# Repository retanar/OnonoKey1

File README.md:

# OnonoKey1 split keyboard

### Sources for used and modified footprints

Maybe didn't use many footprints from them, but at least these were useful.

- https://github.com/joe-scotto/keyswitch-kicad-library
- https://github.com/daprice/keyswitches.pretty

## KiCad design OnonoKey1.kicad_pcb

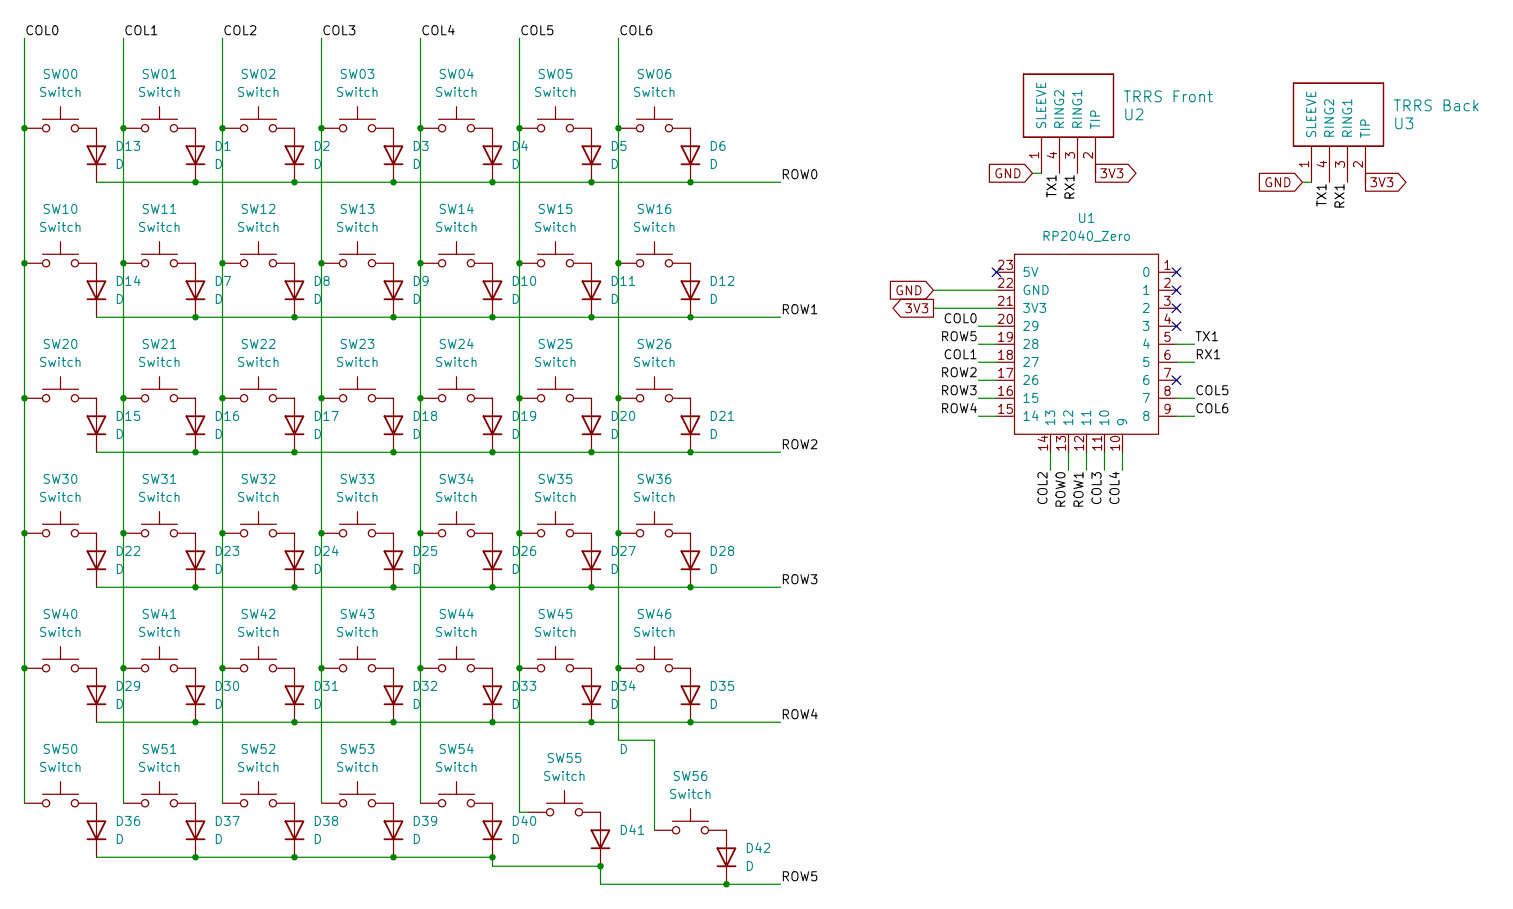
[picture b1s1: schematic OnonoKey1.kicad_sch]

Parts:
D1, D2, D3, D4, D5, D6, D7, D8, D9, D10, D11, D12, D13, D14, D15, D16, D17, D18, D19, D20, D21, D22, D23, D24, D25, D26, D27, D28, D29, D30, D31, D32, D33, D34, D35, D36, D37, D38, D39, D40, D41, D42: D; Diode_DO-35
SW00, SW01, SW02, SW03, SW04, SW05, SW06, SW10, SW11, SW12, SW13, SW14, SW15, SW16, SW20, SW21, SW22, SW23, SW24, SW25, SW26, SW30, SW31, SW32, SW33, SW34, SW35, SW36, SW40, SW41, SW42, SW43, SW44, SW45, SW46, SW50, SW51, SW52, SW53, SW54, SW55, SW56: Switch; Kailh_socket_MX_optional_reversible_1u
U1: RP2040_Zero
U2: TRRS Front; TRRS_PJ-320A
U3: TRRS Back; TRRS_PJ-320A

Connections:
3V3: U1.21 (3V3), U2.2 (TIP), U3.2 (TIP)
/COL0: SW00.1, SW10.1, SW20.1, SW30.1, SW40.1, SW50.1, U1.20 (29)
/COL1: SW01.1, SW11.1, SW21.1, SW31.1, SW41.1, SW51.1, U1.18 (27)
/COL2: SW02.1, SW12.1, SW22.1, SW32.1, SW42.1, SW52.1, U1.14 (13)
/COL3: SW03.1, SW13.1, SW23.1, SW33.1, SW43.1, SW53.1, U1.11 (10)
/COL4: SW04.1, SW14.1, SW24.1, SW34.1, SW44.1, SW54.1, U1.10 (9)
/COL5: SW05.1, SW15.1, SW25.1, SW35.1, SW45.1, SW55.1, U1.8 (7)
/COL6: SW06.1, SW16.1, SW26.1, SW36.1, SW46.1, SW56.1, U1.9 (8)
/ROW0: D1.1 (K), D2.1 (K), D3.1 (K), D4.1 (K), D5.1 (K), D6.1 (K), D13.1 (K), U1.13 (12)
/ROW1: D7.1 (K), D8.1 (K), D9.1 (K), D10.1 (K), D11.1 (K), D12.1 (K), D14.1 (K), U1.12 (11)
/ROW2: D15.1 (K), D16.1 (K), D17.1 (K), D18.1 (K), D19.1 (K), D20.1 (K), D21.1 (K), U1.17 (26)
/ROW3: D22.1 (K), D23.1 (K), D24.1 (K), D25.1 (K), D26.1 (K), D27.1 (K), D28.1 (K), U1.16 (15)
/ROW4: D29.1 (K), D30.1 (K), D31.1 (K), D32.1 (K), D33.1 (K), D34.1 (K), D35.1 (K), U1.15 (14)
/ROW5: D36.1 (K), D37.1 (K), D38.1 (K), D39.1 (K), D40.1 (K), D41.1 (K), D42.1 (K), U1.19 (28)
/RX1: U1.6 (5), U2.3 (RING1), U3.3 (RING1)
/TX1: U1.5 (4), U2.4 (RING2), U3.4 (RING2)
GND: U1.22 (GND), U2.1 (SLEEVE), U3.1 (SLEEVE)
unnamed: D1.2 (A), SW01.2
unnamed: D2.2 (A), SW02.2
unnamed: D3.2 (A), SW03.2
unnamed: D4.2 (A), SW04.2
unnamed: D5.2 (A), SW05.2
unnamed: D6.2 (A), SW06.2
unnamed: D7.2 (A), SW11.2
unnamed: D8.2 (A), SW12.2
unnamed: D9.2 (A), SW13.2
unnamed: D10.2 (A), SW14.2
unnamed: D11.2 (A), SW15.2
unnamed: D12.2 (A), SW16.2
unnamed: D13.2 (A), SW00.2
unnamed: D14.2 (A), SW10.2
unnamed: D15.2 (A), SW20.2
unnamed: D16.2 (A), SW21.2
unnamed: D17.2 (A), SW22.2
unnamed: D18.2 (A), SW23.2
unnamed: D19.2 (A), SW24.2
unnamed: D20.2 (A), SW25.2
unnamed: D21.2 (A), SW26.2
unnamed: D22.2 (A), SW30.2
unnamed: D23.2 (A), SW31.2
unnamed: D24.2 (A), SW32.2
unnamed: D25.2 (A), SW33.2
unnamed: D26.2 (A), SW34.2
unnamed: D27.2 (A), SW35.2
unnamed: D28.2 (A), SW36.2
unnamed: D29.2 (A), SW40.2
unnamed: D30.2 (A), SW41.2
unnamed: D31.2 (A), SW42.2
unnamed: D32.2 (A), SW43.2
unnamed: D33.2 (A), SW44.2
unnamed: D34.2 (A), SW45.2
unnamed: D35.2 (A), SW46.2
unnamed: D36.2 (A), SW50.2
unnamed: D37.2 (A), SW51.2
unnamed: D38.2 (A), SW52.2
unnamed: D39.2 (A), SW53.2
unnamed: D40.2 (A), SW54.2
unnamed: D41.2 (A), SW55.2
unnamed: D42.2 (A), SW56.2

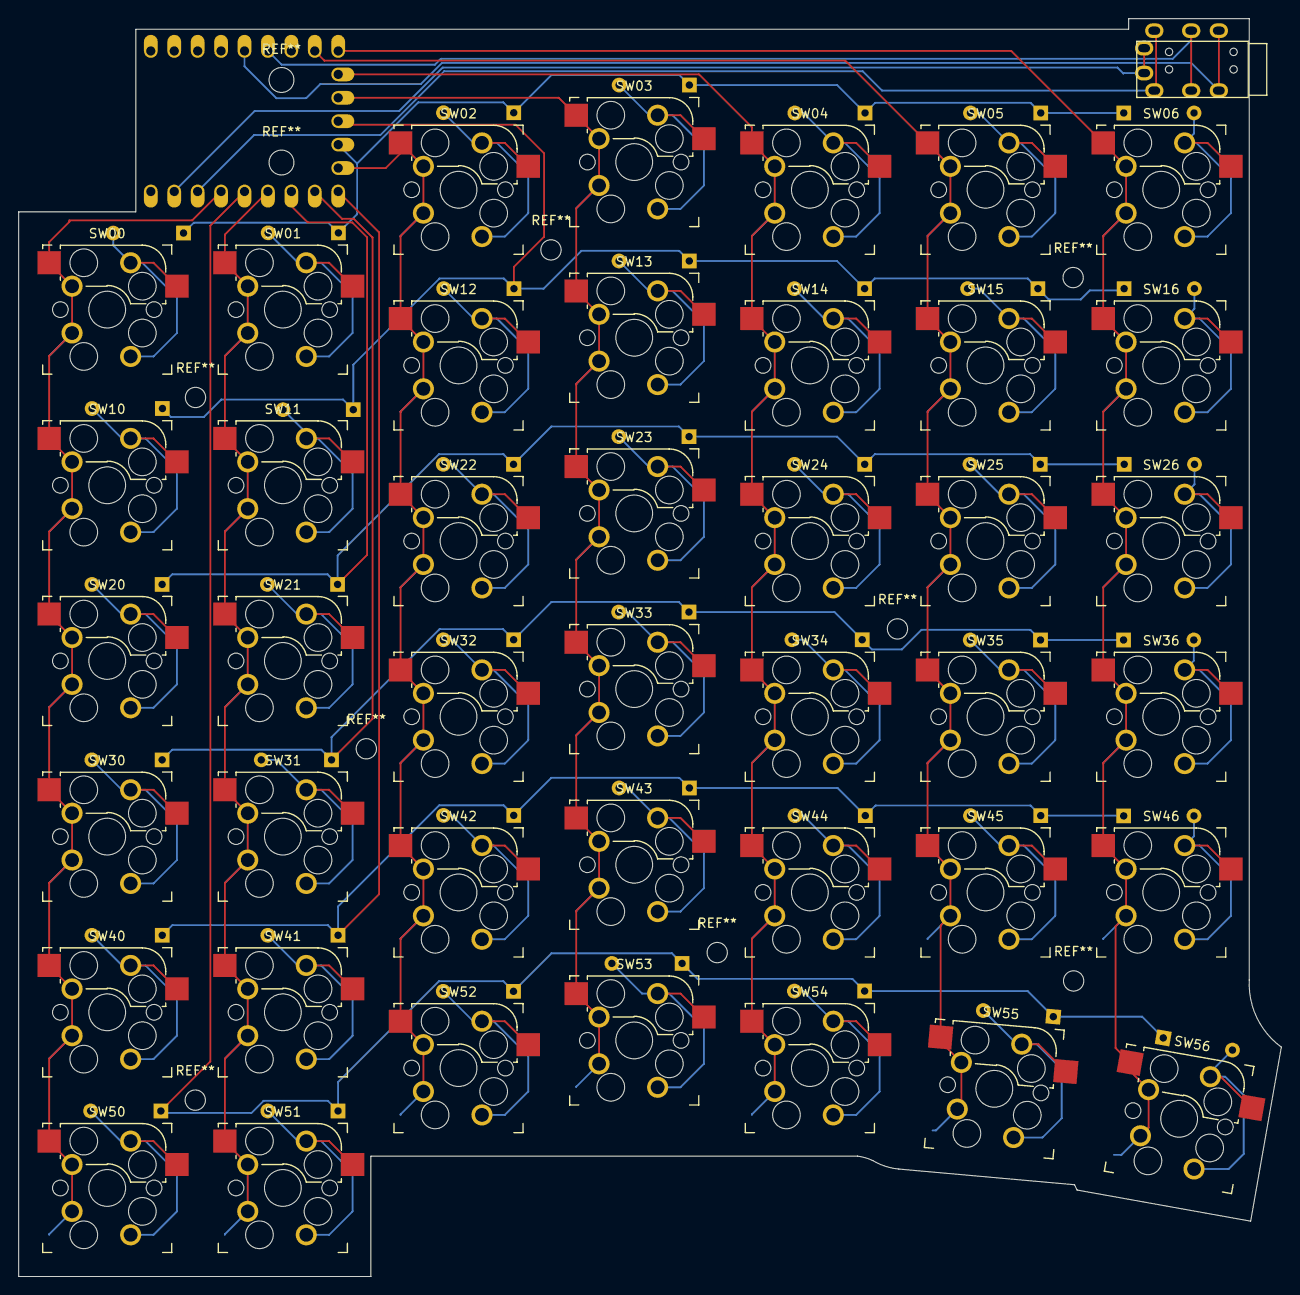
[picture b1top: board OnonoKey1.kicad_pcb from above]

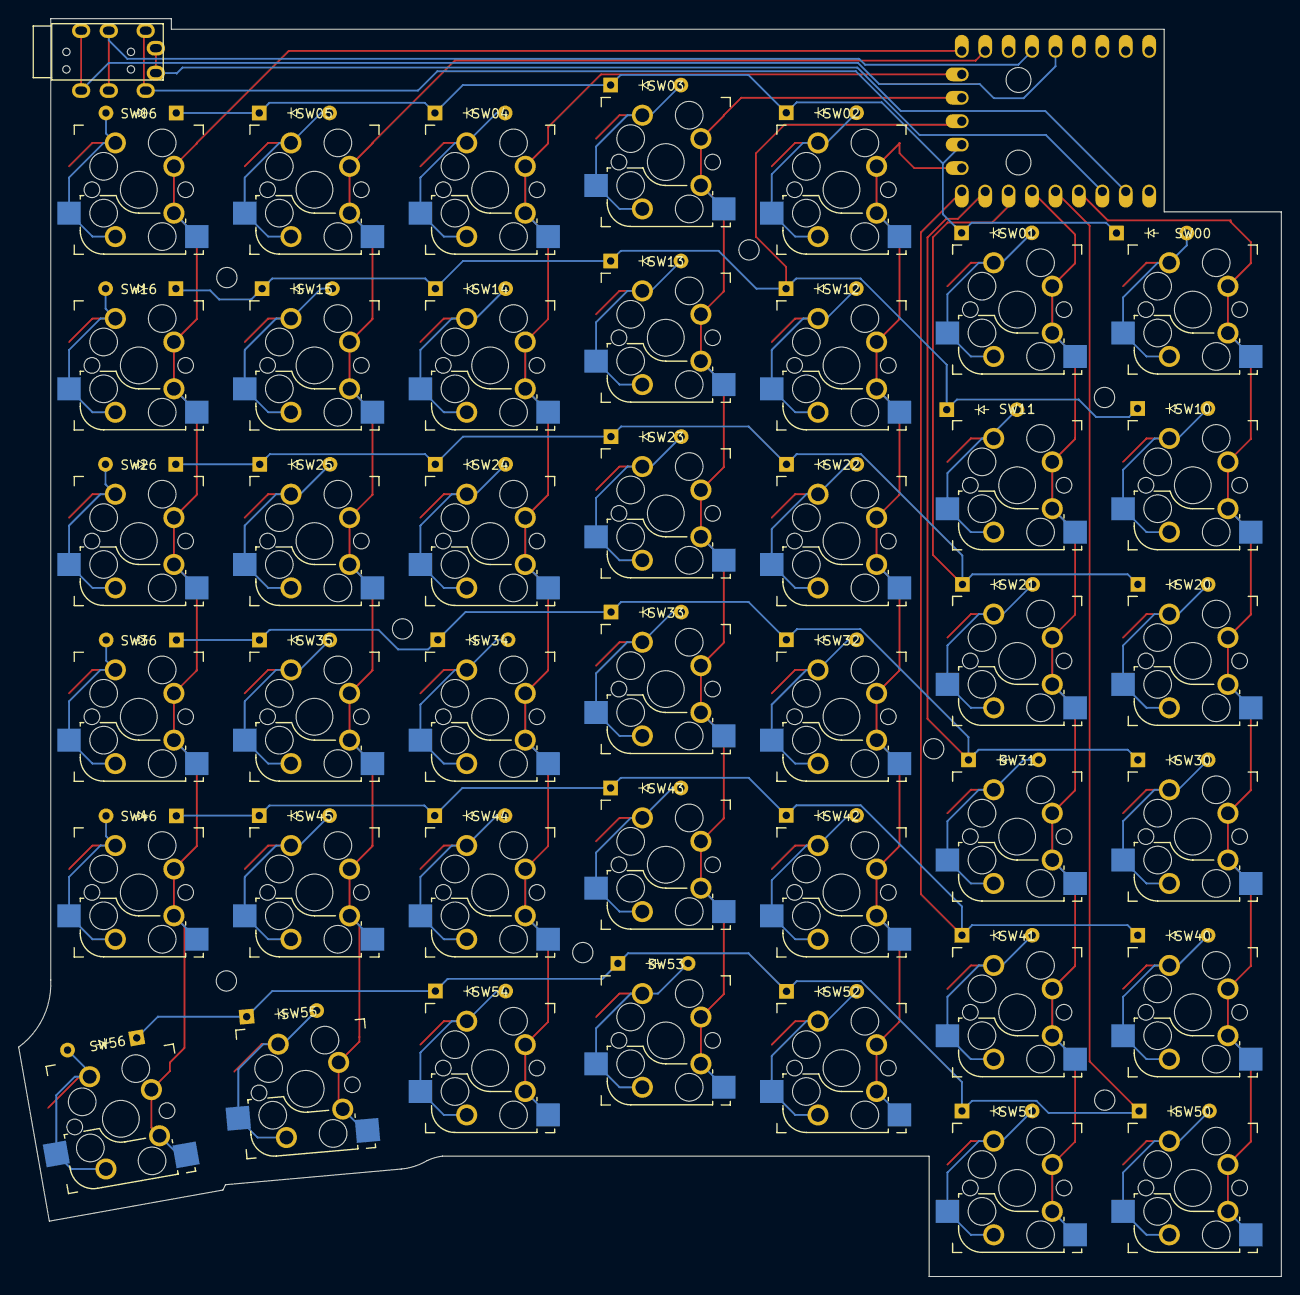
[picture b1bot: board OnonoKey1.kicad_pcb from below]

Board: 2 copper layers, 136.9 x 136.4 mm, 87 parts (43 on the bottom side), 59 nets.

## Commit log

2024-08-04 Changed footprints, rearranged keys on pcb
2024-08-10 Added M2 holes and two TRRS jacks for front and back
2024-08-16 some messing around without any result
2024-08-17 Rearranging board outline, finishing optimising pins for routing, moving upper trrs jack down a little, connecting everything, making DRC errorless
2024-08-17 Small changes including some tolerances, generating gerbers
2024-08-18 Added two 2.7 holes for buttons access on upside down RP2040 Zero. Generated new gerbers for it
2025-06-14 Included qmk files in this folder, and updated pcb with something I don't remember now
2025-06-14 Included used footprints and links to sources, hopefully pcb file works out of the box
